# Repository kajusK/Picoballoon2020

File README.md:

Picoballoon Challenge 2020, Deadbadger probe
============================================

This probe was designed [Picoballoon Challenge](https://www.hvezdarna.cz/?p=8167)
organised by Brno Observatory and Planetarium. A goal of this competition
is to make a probe under 20 grams that would be launched on ballon to altitudes
around 5-15 km. Only requirement except weight is sending altitude of the probe.

A detailed description is available at [deadbadger.cz](https://deadbadger.cz/projects/picoballoon-2020),
tracking site is at [bal.deadbadger.cz](https://bal.deadbadger.cz).

The probe contains
  * STM32F030 MCU
  * MS5607 Pressure and temperature sensor
  * Si7020 Relative humidity sensor
  * SIM28ML GPS module
  * RFM95 LoRa Transceiver
  * MCP1640 based solar supercap charger (optinal)
  * 3.3 V boost regulator with 2.7 V startup supervisor

Firmware
--------
As the commonly used [LMIC](https://github.com/matthijskooijman/arduino-lmic/tree/master/src)
library is quite bulky and far from perfect, I wrote my own LoRaWan library
inspired by [TinyLoRa](https://github.com/adafruit/TinyLoRa).

The main loop does about this:
  * Power up, initialize peripherals
  * Power on GPS
  * Measure system voltages, pressure, humidity
  * Wait for GPS data or timeout
  * Power off GPS
  * Send data over LoRa (ABP, unconfirmed uplink)
  * Unlock power latch (keeps probe powered when supercap voltage drops below 2.7 V)
  * Sleep for 30 minutes
  * Repeat (GPS is powered on every 4 cycles)

Hardware
--------
The board was designed for 0.6 mm thick two sided PCB to reduce weight as
much as possible. Using thicker boards (usually 1.6 mm) changes the antenna
trace impedance, but it should not be that significant.

The solar supercap charger can be snapped off if the probe is powered by battery

Frontend
--------
Data received by [TTN](https://www.thethingsnetwork.org/) are sent over
HTTP integration to custom endpoint written in PHP, it verifies the
auth header and stores data in sqlite database.

User frontend is written in PHP, it shows all received packets in table
and generates flight path on a [map](https://api.mapy.cz).

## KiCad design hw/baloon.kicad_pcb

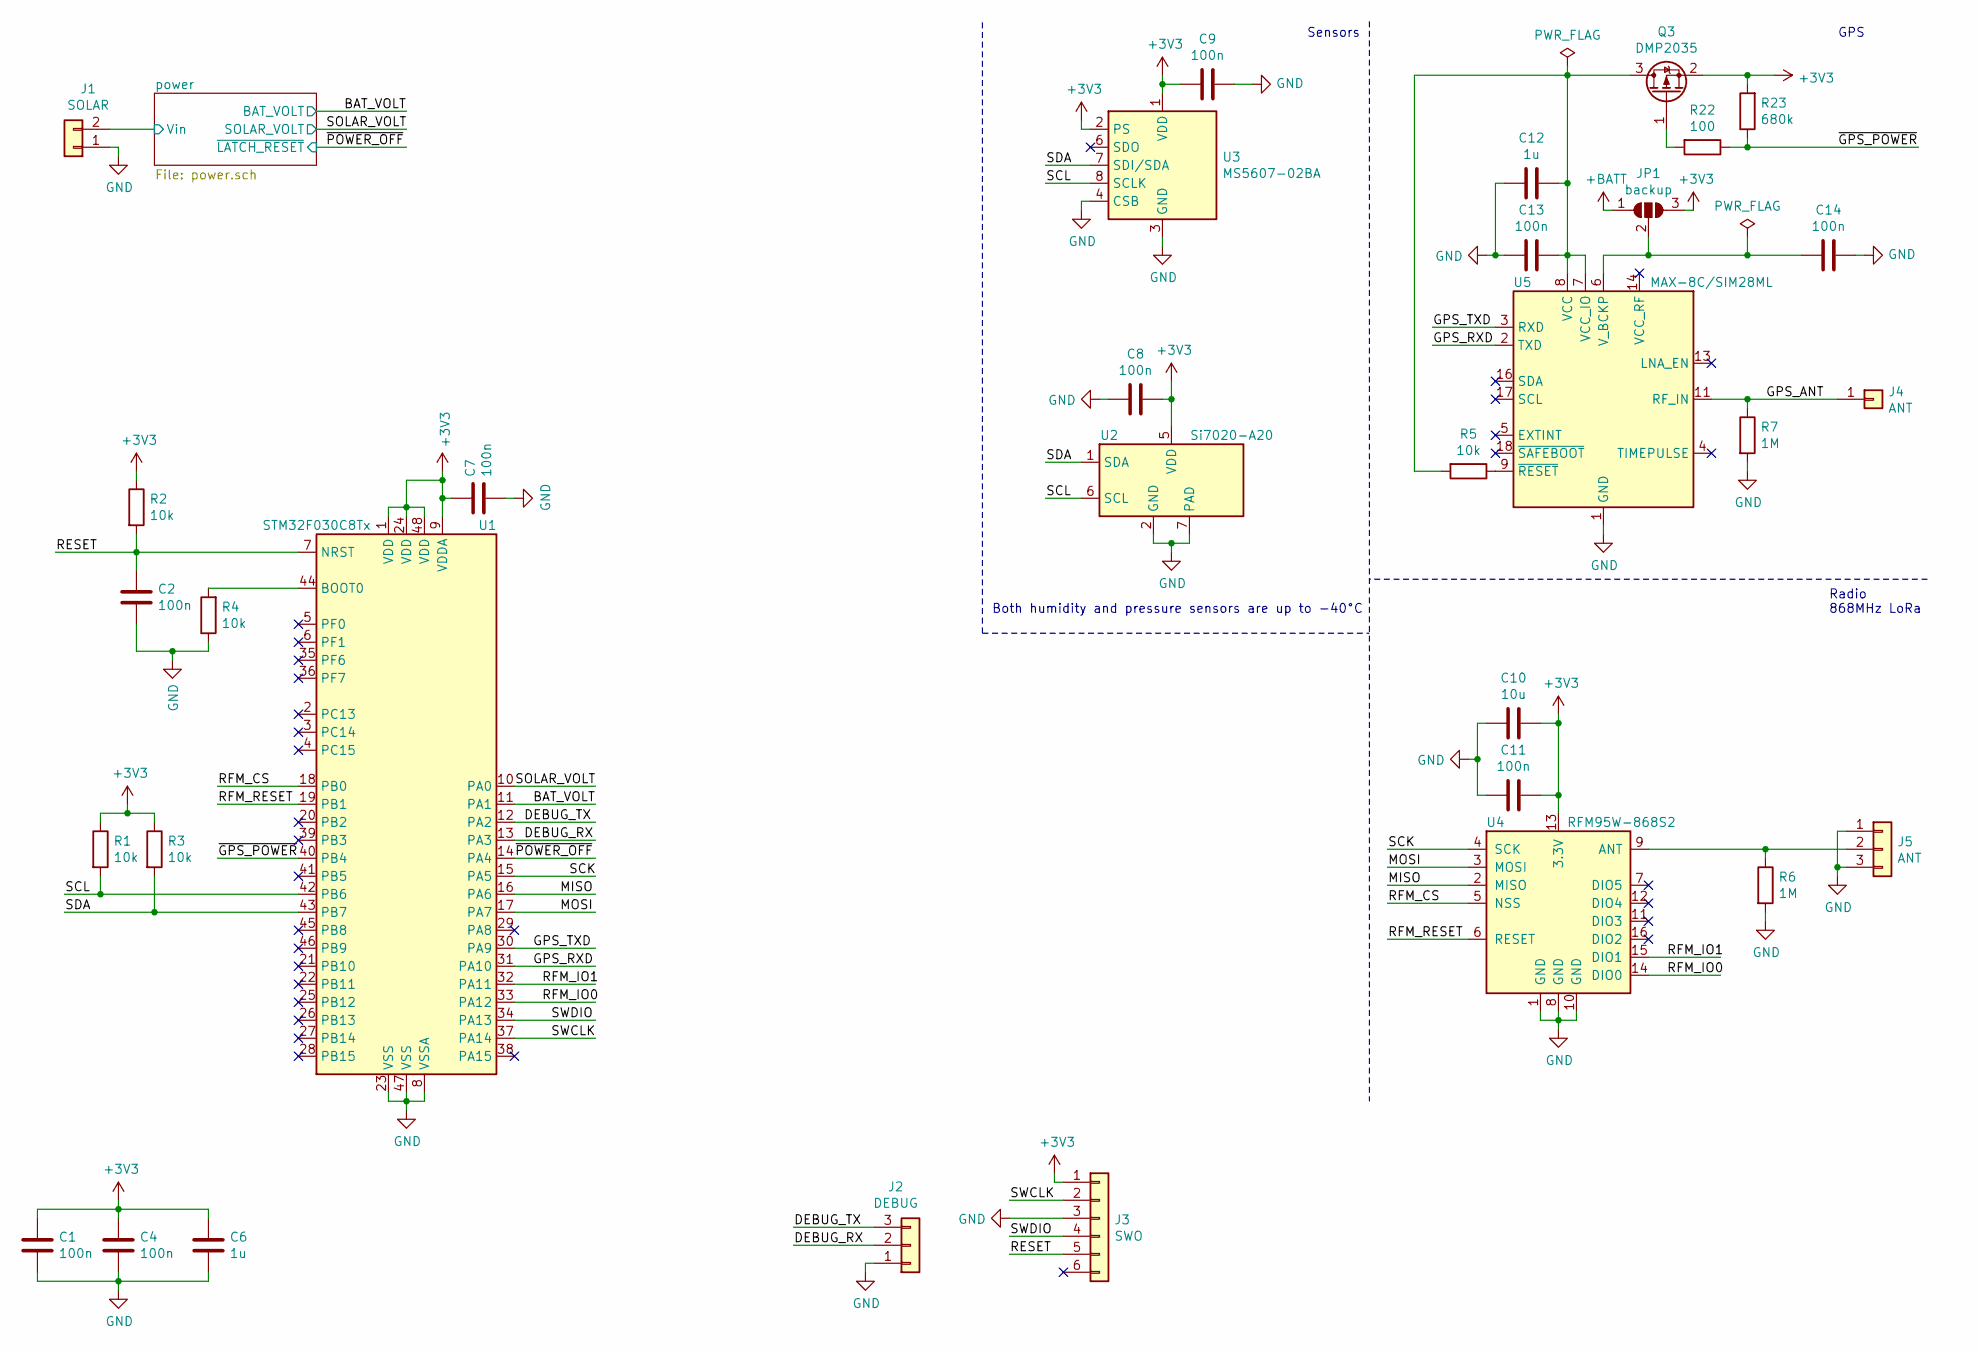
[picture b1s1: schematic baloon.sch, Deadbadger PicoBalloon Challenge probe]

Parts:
C1, C2, C4, C7, C8, C9, C11, C13, C14: 100n; C_0603_1608Metric
C6, C12: 1u; C_0603_1608Metric
C10: 10u; C_0603_1608Metric
J1: SOLAR; PinHeader_1x02_P2.54mm_Vertical
J2: DEBUG; PinSocket_1x03_P1.00mm_Vertical_SMD_Pin1Left
J3: SWO; PinHeader_2x03_P1.27mm_Vertical_SMD
J4: ANT; SolderWirePad_1x01_Drill1mm
J5: ANT; SolderWirePad_1x03_P3.175mm_Drill0.8mm
JP1: backup; SolderJumper-3_P1.3mm_Open_RoundedPad1.0x1.5mm
Q3: DMP2035; SOT-23
R1, R2, R3, R4, R5: 10k; R_0603_1608Metric
R6, R7: 1M; R_0603_1608Metric
R22: 100; R_0603_1608Metric
R23: 680k; R_0603_1608Metric
U1: STM32F030C8Tx; LQFP-48_7x7mm_P0.5mm
U2: Si7020-A20; DFN-6-1EP_3x3mm_P1mm_EP1.5x2.4mm
U3: MS5607-02BA; LGA-8_3x5mm_P1.25mm
U4: RFM95W-868S2; HOPERF_RFM9XW_SMD
U5: MAX-8C/SIM28ML; ublox_MAX

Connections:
+3V3: C1.1, C4.1, C6.1, C7.1, C8.1, C9.2, C10.1, C11.1, J3.1, JP1.3 (B), Q3.2 (S), R1.1, R2.1, R3.1, R23.2, U1.1 (VDD), U1.9 (VDDA), U1.24 (VDD), U1.48 (VDD), U2.5 (VDD), U3.1 (VDD), U3.2 (PS), U4.13 (3.3V); also elsewhere on the board
+BATT: JP1.1 (A); also elsewhere on the board
/BAT_VOLT: U1.11 (PA1); also elsewhere on the board
/DEBUG_RX: J2.2, U1.13 (PA3)
/DEBUG_TX: J2.3, U1.12 (PA2)
/GPS_ANT: J4.1, R7.1, U5.11 (RF_IN)
/GPS_RXD: U1.31 (PA10), U5.2 (TXD)
/GPS_TXD: U1.30 (PA9), U5.3 (RXD)
/MISO: U1.16 (PA6), U4.2 (MISO)
/MOSI: U1.17 (PA7), U4.3 (MOSI)
/RESET: C2.1, J3.5, R2.2, U1.7 (NRST)
/RFM_CS: U1.18 (PB0), U4.5 (NSS)
/RFM_IO0: U1.33 (PA12), U4.14 (DIO0)
/RFM_IO1: U1.32 (PA11), U4.15 (DIO1)
/RFM_RESET: U1.19 (PB1), U4.6 (RESET)
/SCK: U1.15 (PA5), U4.4 (SCK)
/SCL: R1.2, U1.42 (PB6), U2.6 (SCL), U3.8 (SCLK)
/SDA: R3.2, U1.43 (PB7), U2.1 (SDA), U3.7 (SDI/SDA)
/SOLAR_VOLT: U1.10 (PA0); also elsewhere on the board
/SWCLK: J3.2, U1.37 (PA14)
/SWDIO: J3.4, U1.34 (PA13)
/power/Vin: J1.2; also elsewhere on the board
/~GPS_POWER: R22.1, R23.1, U1.40 (PB4)
/~POWER_OFF: U1.14 (PA4); also elsewhere on the board
GND: C1.2, C2.2, C4.2, C6.2, C7.2, C8.2, C9.1, C10.2, C11.2, C12.2, C13.2, C14.1, J1.1, J2.1, J3.3, J5.1, J5.3, R4.1, R6.2, R7.2, U1.8 (VSSA), U1.23 (VSS), U1.47 (VSS), U2.2 (GND), U2.7 (PAD), U3.3 (GND), U3.4 (CSB), U3.5 (CSB), U4.1 (GND), U4.8 (GND), U4.10 (GND), U5.1 (GND), U5.10 (GND), U5.12 (GND); also elsewhere on the board
unnamed: C12.1, C13.1, Q3.3 (D), R5.2, U5.7 (VCC_IO), U5.8 (VCC)
unnamed: C14.2, JP1.2 (C), U5.6 (V_BCKP)
unnamed: J5.2, R6.1, U4.9 (ANT)
unnamed: Q3.1 (G), R22.2
unnamed: R4.2, U1.44 (BOOT0)
unnamed: R5.1, U5.9 (~RESET)

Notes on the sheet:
Radio 868MHz LoRa
GPS
Sensors
Both humidity and pressure sensors are up to -40°C

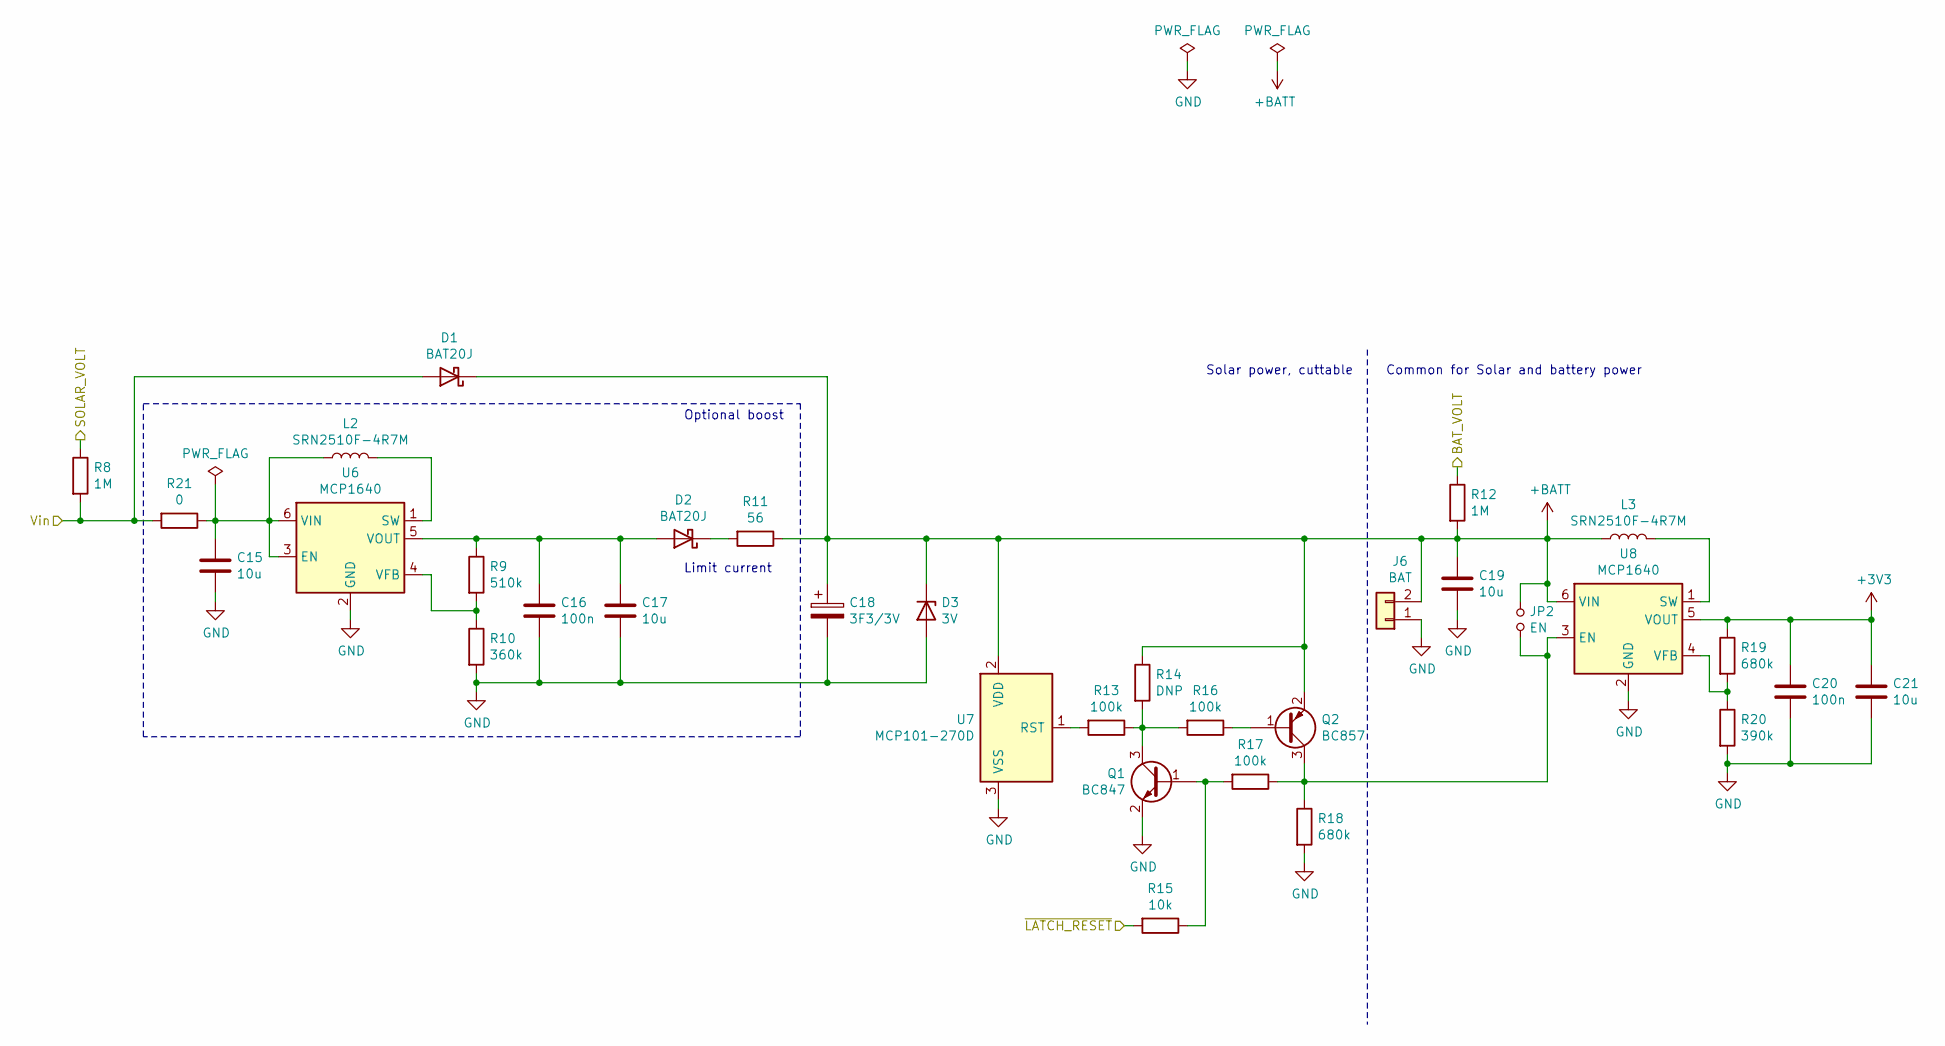
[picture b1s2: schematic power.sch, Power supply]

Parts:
C15, C17, C19, C21: 10u; C_0603_1608Metric
C16, C20: 100n; C_0603_1608Metric
C18: 3F3/3V; R_LDR_5.2x5.2mm_P3.5mm_Horizontal
D1, D2: BAT20J; D_SOD-323
D3: 3V; D_SOD-323
J6: BAT; PinHeader_1x02_P2.54mm_Vertical
JP2: EN; SolderJumper-2_P1.3mm_Open_RoundedPad1.0x1.5mm
L2, L3: SRN2510F-4R7M; L_Abracon_ASPI-3012S
Q1: BC847; SOT-23
Q2: BC857; SOT-23
R8, R12: 1M; R_0603_1608Metric
R9: 510k; R_0603_1608Metric
R10: 360k; R_0603_1608Metric
R11: 56; R_0603_1608Metric
R13, R16, R17: 100k; R_0603_1608Metric
R14: DNP; R_0603_1608Metric
R15: 10k; R_0603_1608Metric
R18, R19: 680k; R_0603_1608Metric
R20: 390k; R_0603_1608Metric
R21: 0; R_0603_1608Metric
U6, U8: MCP1640; SOT-23-6
U7: MCP101-270D; SOT-23

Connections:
+3V3: C20.1, C21.1, R19.1, U8.5 (VOUT); also elsewhere on the board
+BATT: C18.1, C19.1, D1.1 (K), D3.1 (K), J6.2, JP2.1, L3.1, Q2.2 (E), R11.1, R12.2, R14.1, U7.2 (VDD), U8.6 (VIN); also elsewhere on the board
/BAT_VOLT: R12.1; also elsewhere on the board
/SOLAR_VOLT: R8.1; also elsewhere on the board
/power/Vin: D1.2 (A), R8.2, R21.2; also elsewhere on the board
/~POWER_OFF: R15.2; also elsewhere on the board
GND: C15.2, C16.2, C17.2, C18.2, C19.2, C20.2, C21.2, D3.2 (A), J6.1, Q1.2 (E), R10.2, R18.2, R20.2, U6.2 (GND), U7.3 (VSS), U8.2 (GND); also elsewhere on the board
unnamed: C15.1, L2.1, R21.1, U6.3 (EN), U6.6 (VIN)
unnamed: C16.1, C17.1, D2.2 (A), R9.1, U6.5 (VOUT)
unnamed: D2.1 (K), R11.2
unnamed: JP2.2, Q2.3 (C), R17.1, R18.1, U8.3 (EN)
unnamed: L2.2, U6.1 (SW)
unnamed: L3.2, U8.1 (SW)
unnamed: Q1.1 (B), R15.1, R17.2
unnamed: Q1.3 (C), R13.1, R14.2, R16.2
unnamed: Q2.1 (B), R16.1
unnamed: R9.2, R10.1, U6.4 (VFB)
unnamed: R13.2, U7.1 (RST)
unnamed: R19.2, R20.1, U8.4 (VFB)

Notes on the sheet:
Limit current
Optional boost
Common for Solar and battery power
Solar power, cuttable

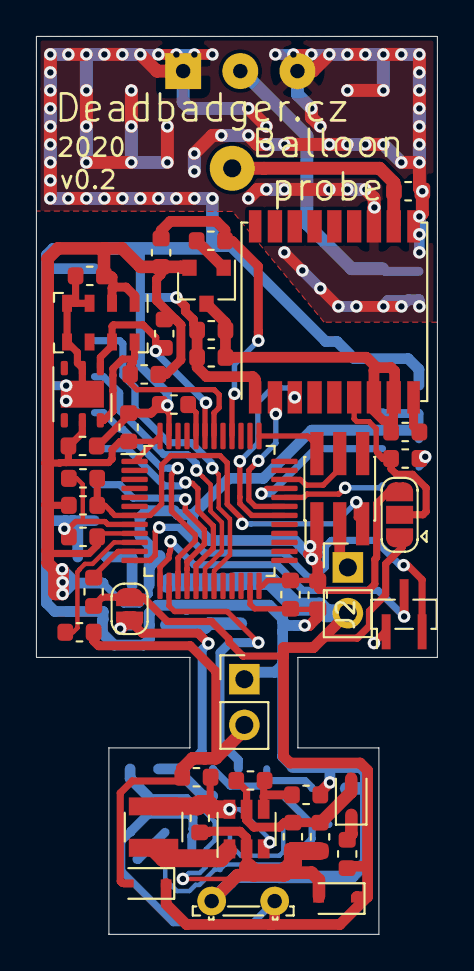
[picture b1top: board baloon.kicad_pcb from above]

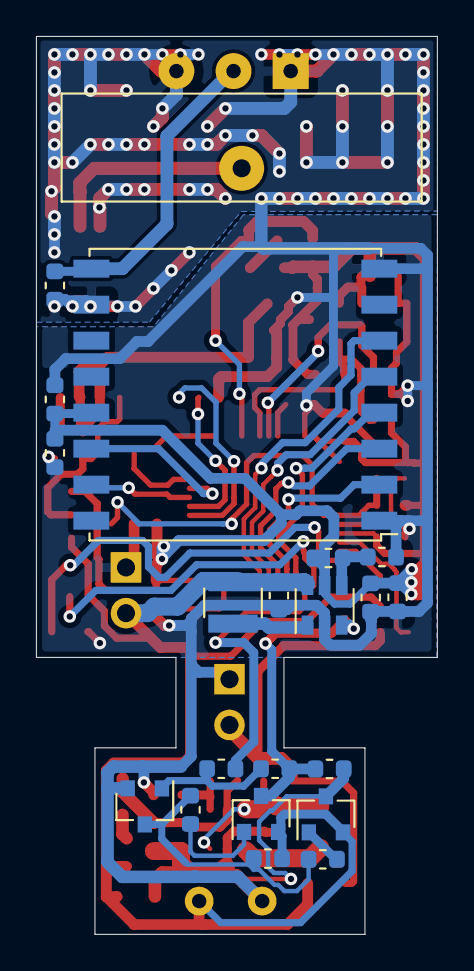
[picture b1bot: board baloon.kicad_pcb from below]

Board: 2 copper layers, 22.3 x 49.9 mm, 66 parts (20 on the bottom side), 43 nets.

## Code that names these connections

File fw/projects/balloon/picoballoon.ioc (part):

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Mcu.Name=STM32F030C8Tx
Mcu.Package=LQFP48
Mcu.UserName=STM32F030C8Tx
PA0.GPIOParameters=GPIO_Label
PA0.GPIO_Label=SOLAR_VOLT
PA0.Mode=IN0
PA0.Signal=ADC_IN0
PA1.GPIOParameters=GPIO_Label
PA1.GPIO_Label=BAT_VOLT
PA1.Mode=IN1
PA1.Signal=ADC_IN1
PA10.GPIOParameters=GPIO_Label
PA10.GPIO_Label=GPS_RX
PA10.Mode=Asynchronous
PA10.Signal=USART1_RX
PA11.GPIOParameters=GPIO_Label
PA11.GPIO_Label=RFM_IO0
PA11.Signal=GPIO_Input
PA12.GPIOParameters=GPIO_Label
PA12.GPIO_Label=RFM_IO1
PA12.Signal=GPIO_Input
PA13.Mode=Serial_Wire
PA13.Signal=SYS_SWDIO
PA14.Mode=Serial_Wire
PA14.Signal=SYS_SWCLK
PA2.GPIOParameters=GPIO_Label
PA2.GPIO_Label=DEBUG_TX
PA2.Mode=Asynchronous
PA2.Signal=USART2_TX
PA3.GPIOParameters=GPIO_Label
PA3.GPIO_Label=DEBUG_RX
PA3.Mode=Asynchronous
PA3.Signal=USART2_RX
PA4.GPIOParameters=PinState,GPIO_Label
PA4.GPIO_Label=POWER_OFF_N
PA4.PinState=GPIO_PIN_SET
PA4.Signal=GPIO_Output
PA5.Mode=Full_Duplex_Master
PA5.Signal=SPI1_SCK
PA6.Mode=Full_Duplex_Master
PA6.Signal=SPI1_MISO
PA7.Mode=Full_Duplex_Master
PA7.Signal=SPI1_MOSI
PA9.GPIOParameters=GPIO_Label
PA9.GPIO_Label=GPS_TX
PA9.Mode=Asynchronous
PA9.Signal=USART1_TX
PB0.GPIOParameters=PinState,GPIO_Label
PB0.GPIO_Label=RFM_CS
PB0.PinState=GPIO_PIN_SET
PB0.Signal=GPIO_Output
PB1.GPIOParameters=PinState,GPIO_Label
PB1.GPIO_Label=RFM_RESET
PB1.PinState=GPIO_PIN_RESET
PB1.Signal=GPIO_Output
PB4.GPIOParameters=PinState,GPIO_Label
PB4.GPIO_Label=GPS_POWER_N
PB4.PinState=GPIO_PIN_SET
PB4.Signal=GPIO_Output
PB6.Mode=I2C
PB6.Signal=I2C1_SCL
PB7.Mode=I2C
PB7.Signal=I2C1_SDA
board=custom

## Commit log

2020-01-22 Final board
2020-01-29 Fixed header lock name
2020-01-29 Added power control
2020-01-29 Added extended interrupts control
2020-01-29 Wait for rtc synchronization after wake up
2020-01-29 Enable both interrupt and event for exti
2020-01-29 Added alarm support, cleared up the rtc driver
2020-02-05 Added aes128 encryption
2020-02-05 Added tests
2020-02-05 Fixed typo
2020-02-12 Added cmac to aes
2020-02-14 Added LoRaWan ABP unconfirmed upling
2020-02-17 Added pressure sensor driver
2020-02-17 Added SI7020 driver
2020-02-21 Added counters reading/writing to lora
2020-02-21 Log info messages by default
2020-02-21 Updated core temp measuring variable (+-128 should be enough for temperatures)
2020-02-21 Added invalidate and fix timestamp to gps driver
2020-02-21 Added rfm module driver
2020-02-21 Added probe logic
2020-02-23 Added payload decoder for TTN
2020-02-23 Added telemetry webpage
2020-02-23 Added readme and license
2020-02-29 Typos, etc fixed
2020-02-29 Fixed rfm transmit command, regenerated lora frequencies by script
2020-02-29 Use PA enabled all the time, RFM95 doesn't transmit when pa disabled as RFO output is not connected
2020-02-29 Added timeouts to infinite wait loops in i2c,...
2020-02-29 Clear flags before running i2c transaction
2020-02-29 Fixed ms5607, added crc checking
2020-02-29 RFM pins are inputs for now
2020-02-29 Added link to crc algorithm
2020-03-01 Added forgotten message termination to nema parser
2020-03-01 Fixed nmea parser on arm - va_list seems not to be a pointer, first argument was used in every call as the ap was copied, not accessed as pointer
2020-03-01 Ignore gga messages with quality equal to zero (invalid)
2020-03-01 Radomize lora channel based on last byte of payload
2020-03-01 Fixed json field selection in php enpoint
2020-03-01 Fixed RTC hal driver
2020-03-01 Fixed reading temperature from ms5607
2020-03-01 Keep gps powered off by default
2020-03-02 Show lora position if gps not available, calculate altitude from pressure
2020-03-02 Both rmc and gga must be present for valid data
2020-03-02 Added images
2020-03-02 Fixed links and images
2020-03-29 Added schematic
2020-03-29 Hotfixes shortly before launch
2020-04-04 Moved common and reusable files to a separate repository
